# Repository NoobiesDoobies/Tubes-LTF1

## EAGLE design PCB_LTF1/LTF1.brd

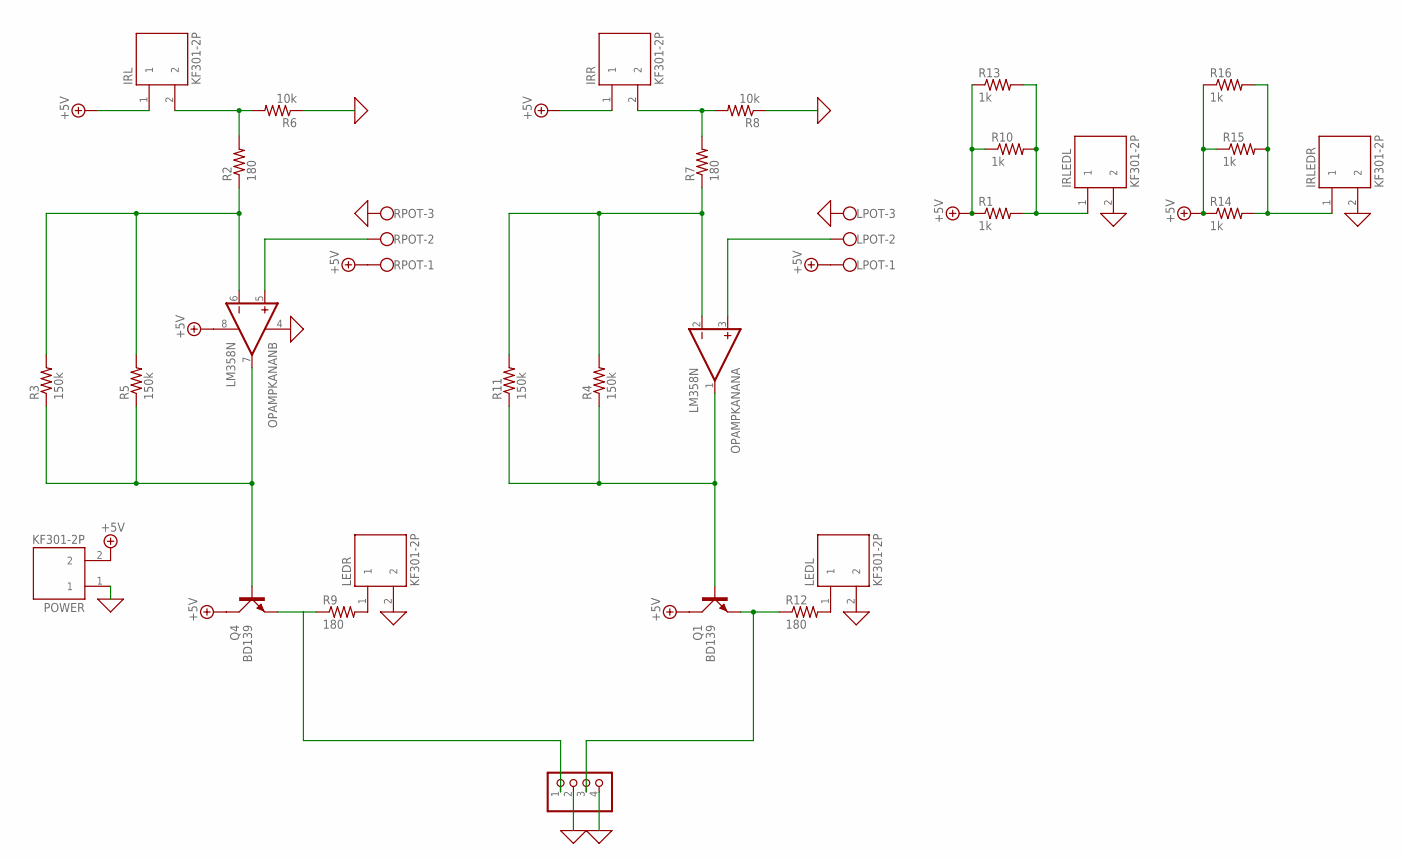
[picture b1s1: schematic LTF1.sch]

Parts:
IRL: KF301-2P; HANDSON_KF301-2P
IRLEDL: KF301-2P; HANDSON_KF301-2P
IRLEDR: KF301-2P; HANDSON_KF301-2P
IRR: KF301-2P; HANDSON_KF301-2P
LEDL: KF301-2P; HANDSON_KF301-2P
LEDR: KF301-2P; HANDSON_KF301-2P
LPOT: W237-103
MOTORDRIVER: PINHD-1X4; 1X04
OPAMPKANAN: LM358N; DIL08
POWER: KF301-2P; HANDSON_KF301-2P
Q1, Q4: BD139; TO126AV
R1, R10, R13, R14, R15, R16: 1k; 0204/7
R2, R7, R9, R12: 180; 0204/7
R3, R4, R5, R11: 150k; 0204/7
R6, R8: 10k; 0204/7
RPOT: W237-103

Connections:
0: IRLEDL.2, IRLEDR.2, LEDL.2, LEDR.2, LPOT.3, MOTORDRIVER.2, MOTORDRIVER.4, OPAMPKANAN.4 (V-), POWER.1, R6.1, R8.1, RPOT.3
+5V: IRL.1, IRR.1, LPOT.1, OPAMPKANAN.8 (V+), POWER.2, Q1.C, Q4.C, R1.1, R10.1, R13.1, R14.1, R15.1, R16.1, RPOT.1
IRKIRI: IRL.2, R2.2, R6.2
LEDIRKANAN: IRLEDL.1, R1.2, R10.2, R13.2
LEDIRKANAN1: IRLEDR.1, R14.2, R15.2, R16.2
MOTORKANAN: OPAMPKANAN.7 (OUT), Q4.B, R3.1, R5.1
MOTORKANAN1: OPAMPKANAN.1 (OUT), Q1.B, R4.1, R11.1
unnamed: LEDR.1, R9.2
unnamed: LEDL.1, R12.2
unnamed: OPAMPKANAN.2 (-IN), R4.2, R7.1, R11.2
unnamed: LPOT.2, OPAMPKANAN.3 (+IN)
unnamed: IRR.2, R7.2, R8.2
unnamed: MOTORDRIVER.3, Q1.E, R12.1
unnamed: OPAMPKANAN.6 (-IN), R2.1, R3.2, R5.2
unnamed: MOTORDRIVER.1, Q4.E, R9.1
unnamed: OPAMPKANAN.5 (+IN), RPOT.2

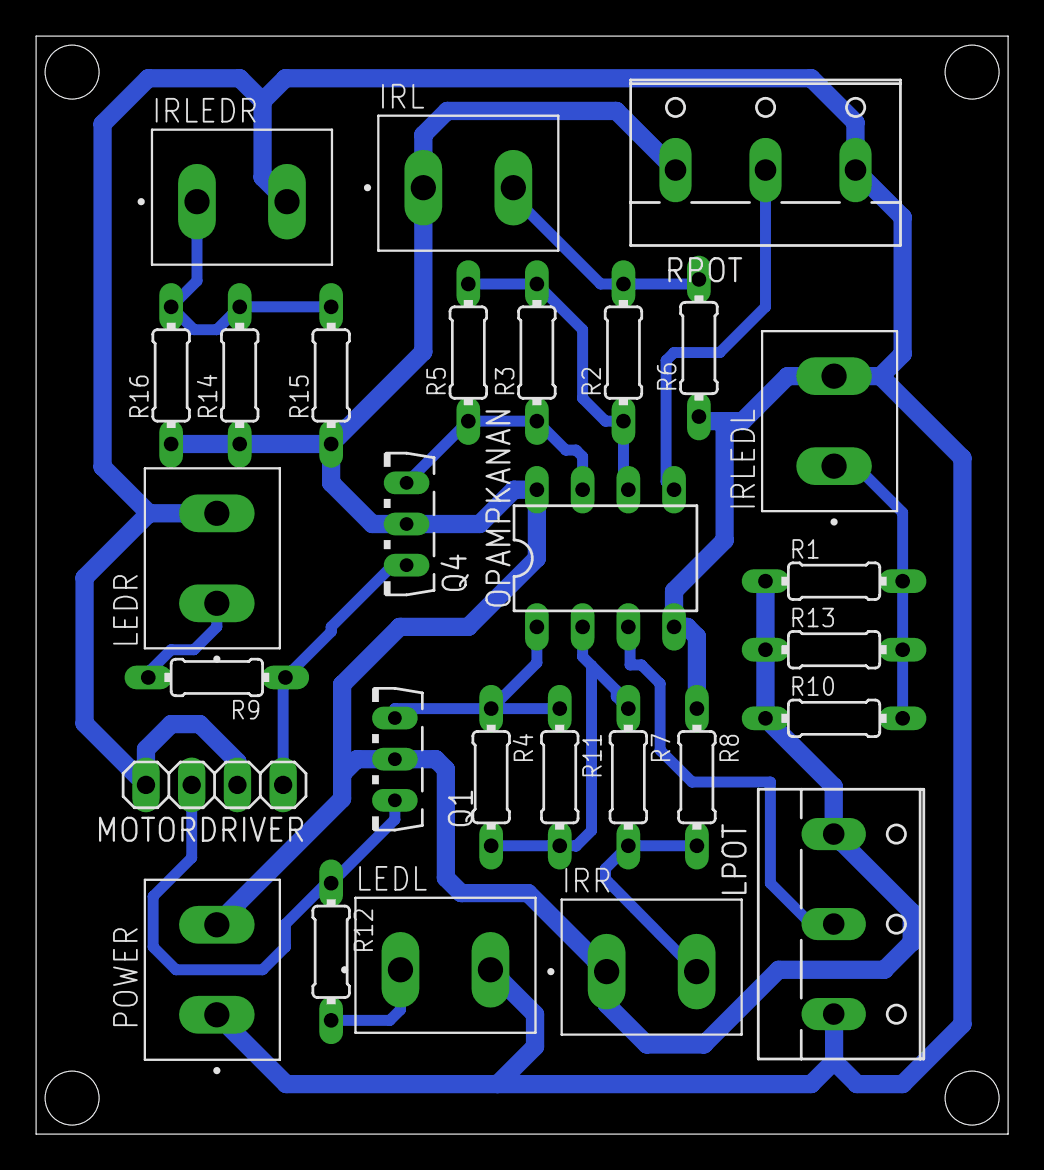
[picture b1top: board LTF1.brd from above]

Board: 2 copper layers, 54.0 x 61.0 mm, 29 parts (0 on the bottom side), 16 nets.

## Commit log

2022-11-15 initial upload
2022-12-11 initial commit sch
2022-12-13 op amp belum kesambung
2022-12-13 done sch
2022-12-14 done routing and PCB :+1:
2022-12-14 add 3d model
2022-12-15 design rule passed
